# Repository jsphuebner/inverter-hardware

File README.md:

# inverter-hardware
Eagle schematics of inverter main board, sensor boards and gate drivers

# License
Attribution-ShareAlike 4.0 International
https://creativecommons.org/licenses/by-sa/4.0/legalcode

You musn't change the copyright info (J. Huebner and openinverter.org) on the silkscreen in size location or content.

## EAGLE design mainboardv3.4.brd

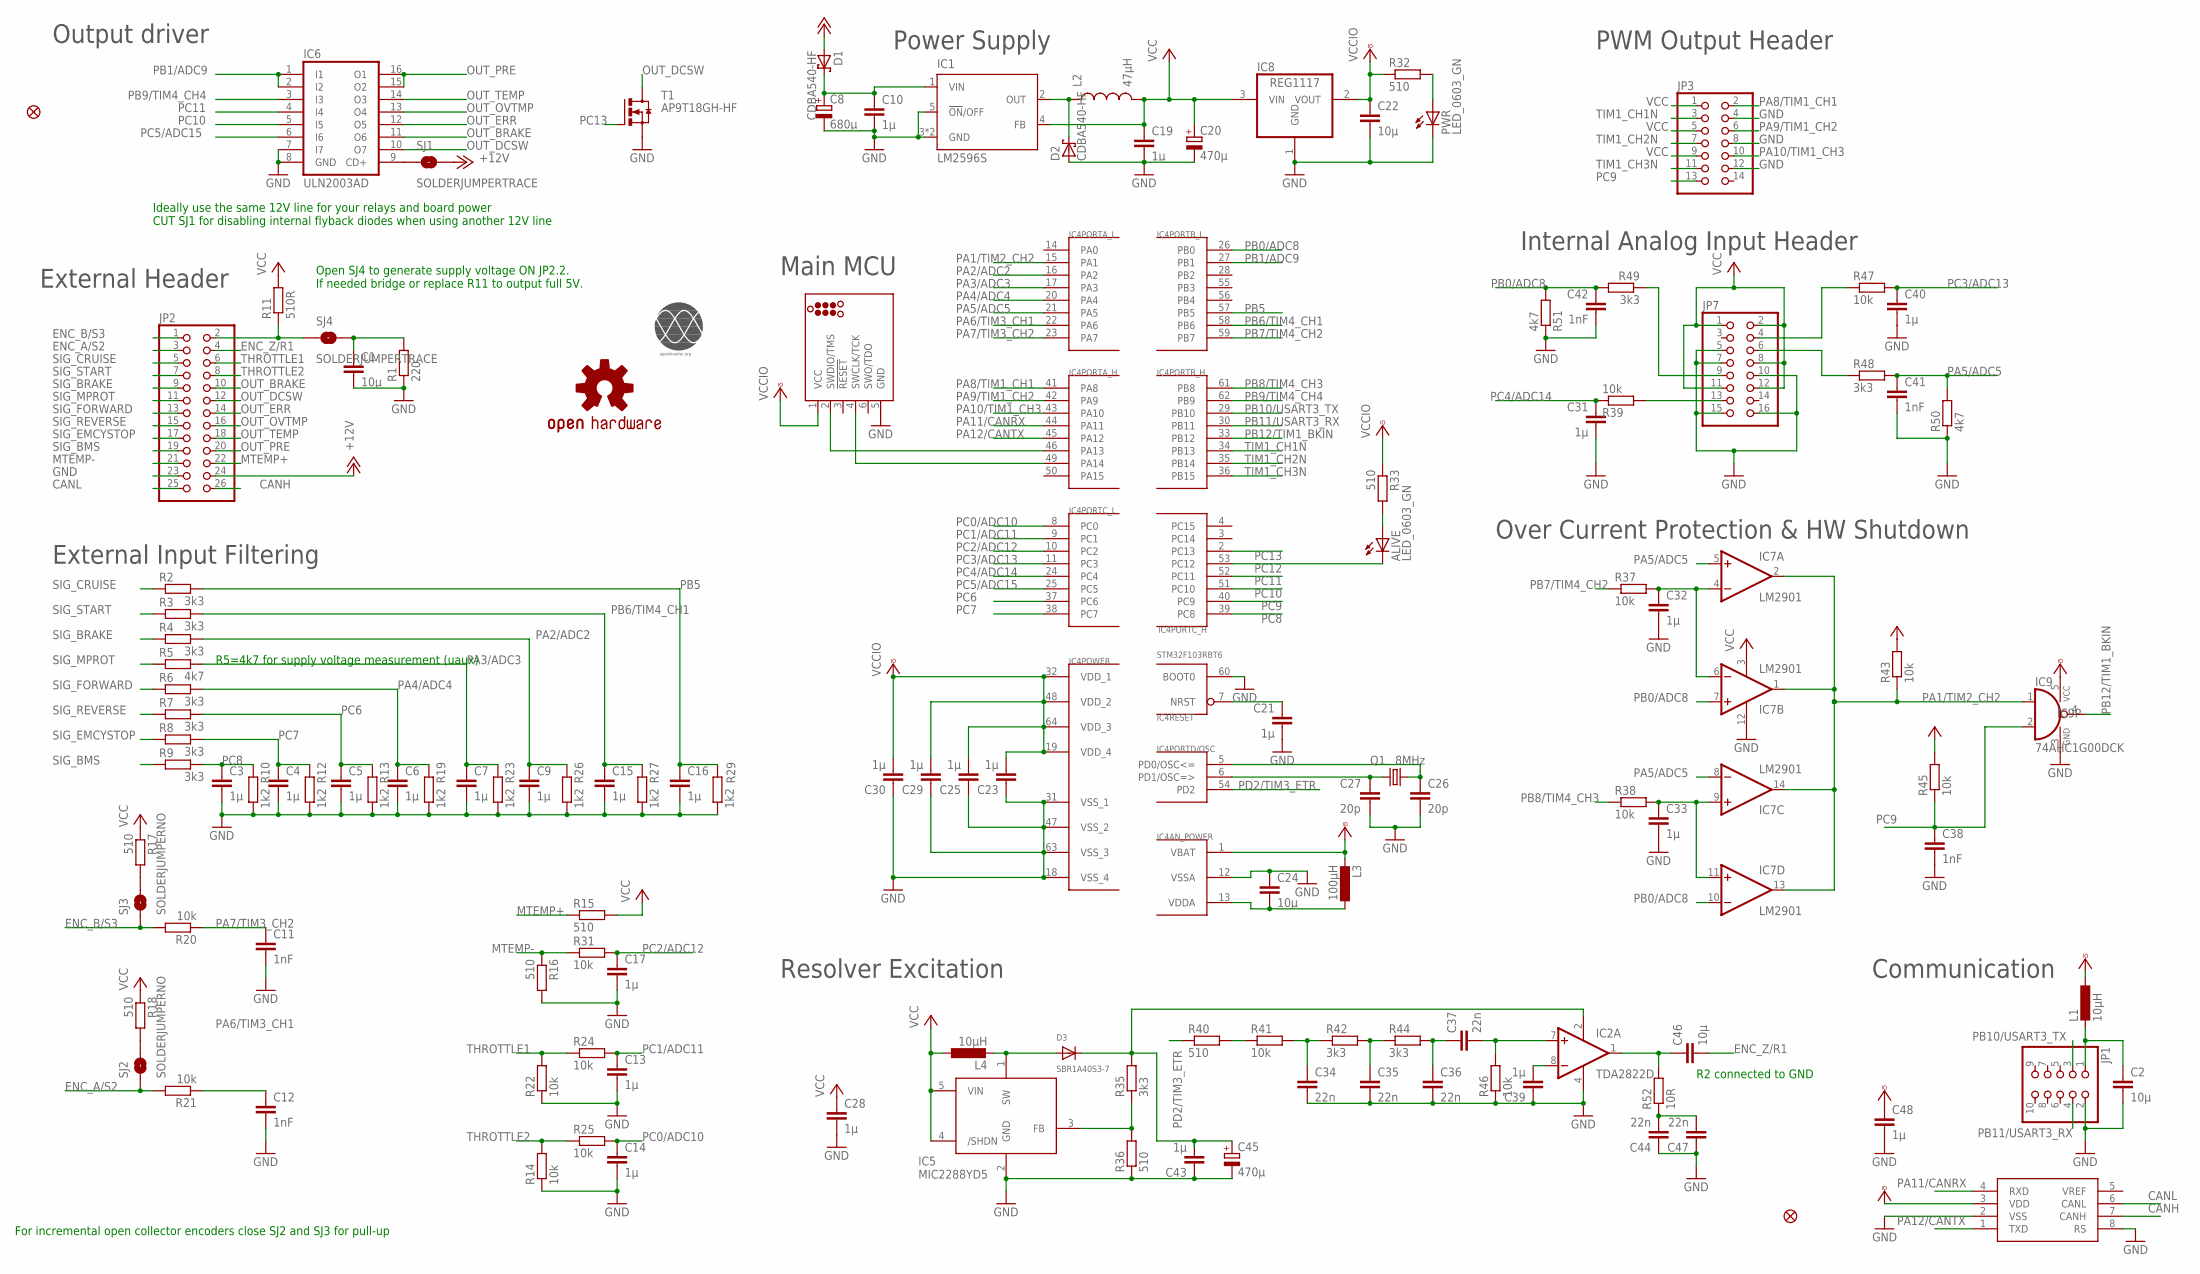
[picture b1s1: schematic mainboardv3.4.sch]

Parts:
ALIVE: LED_0603_GN; SML0805
C1, C2, C22, C46: 10µ; C0805
C3, C4, C5, C6, C7, C9, C10, C13, C14, C15, C16, C17, C19, C21, C23, C25, C28, C29, C30, C31, C32, C33, C39, C40, C43, C48: 1µ; C0603
C8: 680µ; UD-10X10_NICHICON
C11, C12, C38, C41, C42: 1nF; C0603
C20, C45: 470µ; UD-6,3X7,7_NICHICON
C24: 10µ; C0603
C26, C27: 20p; C0603
C34, C35, C36, C37, C44, C47: 22n; C0603
D1, D2: CDBA540-HF; SMB
D3: SBR1A40S3-7; SOD-323F
FID1, FID2: FIDUCIAL1X2.5; FIDUCIAL-1X2.5
IC1: LM2596S; TO263-5
IC2: TDA2822D; SO08
IC3: SN65HVD230DR; SO08
IC4: STM32F103RBT6; TQFP64
IC5: MIC2288YD5; SOT23-5L
IC6: ULN2003AD; SO16
IC7: LM2901; SO14
IC8: REG1117; SOT223
IC9: 74AHC1G00DCK; SC70-5
J1: TC2030_SWD-MCP; TC2030-MCP
JP1: PINHD-2X5/90; 2X05/90
JP2: PINHD-2X13; 2X13
JP3: PINHD-2X7; 2X07
JP7: PINHD-2X8; 2X08
L1: 10µH; L2012C
L2: 47µH; CDRH125
L3: 100µH; L2012C
L4: 10µH; L2825P
LOGO1: OSHW-LOGOM; OSHW-LOGO-M
PWR: LED_0603_GN; SML0805
Q1: 8MHz; CRYSTAL-TXC-7A
R1: 220; R0603
R2, R3, R4, R6, R7, R8, R9, R35, R42, R44, R48, R49: 3k3; R0603
R5, R50, R51: 4k7; R0603
R10, R12, R13, R19, R23, R26, R27, R29: 1k2; R0603
R11: 510R; R0603
R14, R20, R21, R22, R24, R25, R31, R37, R38, R39, R41, R43, R45, R46, R47: 10k; R0603
R15, R16, R17, R18, R32, R33, R36, R40: 510; R0603
R52: 10R; R0603
SJ1, SJ4: SOLDERJUMPERTRACE; SJ_2S-TRACE
SJ2, SJ3: SOLDERJUMPERNO; SJ_2S-NO
T1: AP9T18GH-HF; D-PAK_TO252AA
U$1: OI-LOGO; OI_LOGO

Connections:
+12V: D1.A, JP2.24, SJ1.2
CANH: IC3.7 (CANH), JP2.26
CANL: IC3.6 (CANL), JP2.25
ENC_A/S2: JP2.3, R21.2, SJ2.1
ENC_B/S3: JP2.1, R20.2, SJ3.1
ENC_Z/R1: C46.2, JP2.4
GND: C1.2, C2.2, C3.2, C4.2, C5.2, C6.2, C7.2, C8.-, C9.2, C10.2, C11.2, C12.2, C13.2, C14.2, C15.2, C16.2, C17.2, C19.2, C20.-, C21.2, C22.2, C23.1, C24.1, C25.1, C26.2, C27.2, C28.2, C29.1, C30.1, C31.2, C32.2, C33.2, C34.2, C35.2, C36.2, C38.2, C39.1, C40.2, C41.2, C42.2, C43.1, C44.1, C45.-, C47.1, C48.2, D2.A, IC1.3 (GND), IC1.5 (!ON!/OFF), IC1.6 (GND), IC2.4 (V-), IC3.2 (VSS), IC3.8 (RS), IC4.12 (VSSA), IC4.18 (VSS_4), IC4.31 (VSS_1), IC4.47 (VSS_2), IC4.60 (BOOT0), IC4.63 (VSS_3), IC5.2 (GND), IC6.7 (I7), IC6.8 (GND), IC7.12 (GND), IC8.1 (GND), IC9.3 (GND), J1.5 (GND), JP1.2, JP2.23, JP3.4, JP3.8, JP3.12, JP7.5, JP7.7, JP7.10, JP7.15, JP7.16, PWR.C, R1.1, R10.1, R12.1, R13.1, R14.1, R16.2, R19.1, R22.1, R23.1, R26.1, R27.1, R29.1, R36.1, R46.1, R50.1, R51.1, T1.3 (S)
I_L1: JP7.6, R48.1
I_L2: JP7.9, R49.1
MTEMP+: JP2.22, R15.1
MTEMP-: JP2.21, R16.1, R31.1
unnamed: IC6.9 (CD+), SJ1.1
unnamed: C27.1, IC4.6 (PD1/OSC=>), Q1.P$1 (1)
unnamed: R17.2, SJ3.2
unnamed: C26.1, IC4.5 (PD0/OSC<=), Q1.P$2 (2)
unnamed: IC4.46 (PA13), J1.2 (SWDIO/TMS)
unnamed: IC4.49 (PA14), J1.4 (SWCLK/TCK)
unnamed: C24.2, IC4.13 (VDDA), L3.1
unnamed: R18.2, SJ2.2
unnamed: C1.1, R1.2, SJ4.2
unnamed: C33.1, IC7.9 (+IN), IC7.11 (+IN), R38.2
unnamed: C44.2, C47.2, R52.1
unnamed: R40.2, R41.1
unnamed: D2.C, IC1.2 (OUT), L2.1
unnamed: C32.1, IC7.4 (-IN), IC7.6 (-IN), R37.2
unnamed: C35.1, R42.2, R44.1
unnamed: C36.1, C37.1, R44.2
unnamed: C37.2, IC2.7 (+IN), R46.2
unnamed: C46.1, IC2.1 (OUT), R52.2
unnamed: C43.2, C45.+, D3.C, IC2.2 (V+), R35.2
unnamed: PWR.A, R32.2
unnamed: ALIVE.A, R33.2
unnamed: IC5.3 (FB), R35.1, R36.2
unnamed: C8.+, C10.1, D1.C, IC1.1 (VIN)
unnamed: D3.A, IC5.1 (SW), L4.2
unnamed: C39.2, IC2.8 (-IN)
unnamed: C2.1, JP1.1, L1.2
unnamed: C34.1, R41.2, R42.1
NRST: C21.1, IC4.7 (NRST)
OUT_BRAKE: IC6.11 (O6), JP2.10
OUT_DCSW: IC6.10 (O7), JP2.12, T1.4 (D)
OUT_ERR: IC6.12 (O5), JP2.14
OUT_OVTMP: IC6.13 (O4), JP2.16
OUT_PRE: IC6.15 (O2), IC6.16 (O1), JP2.20
OUT_TEMP: IC6.14 (O3), JP2.18
PA1/TIM2_CH2: IC4.15 (PA1), IC7.1 (OUT), IC7.2 (OUT), IC7.13 (OUT), IC7.14 (OUT), IC9.1 (I0), R43.1
PA2/ADC2: C9.1, IC4.16 (PA2), R4.2, R26.2
PA3/ADC3: C7.1, IC4.17 (PA3), R5.2, R23.2
PA4/ADC4: C6.1, IC4.20 (PA4), R6.2, R19.2
PA5/ADC5: C41.1, IC4.21 (PA5), IC7.5 (+IN), IC7.8 (-IN), R48.2, R50.2
PA6/TIM3_CH1: C12.1, IC4.22 (PA6), R21.1
PA7/TIM3_CH2: C11.1, IC4.23 (PA7), R20.1
PA8/TIM1_CH1: IC4.41 (PA8), JP3.2
PA9/TIM1_CH2: IC4.42 (PA9), JP3.6
PA10/TIM1_CH3: IC4.43 (PA10), JP3.10
PA11/CANRX: IC3.4 (RXD), IC4.44 (PA11)
PA12/CANTX: IC3.1 (TXD), IC4.45 (PA12)
PB0/ADC8: C42.1, IC4.26 (PB0), IC7.7 (+IN), IC7.10 (-IN), R49.2, R51.2
PB1/ADC9: IC4.27 (PB1), IC6.1 (I1), IC6.2 (I2)
PB5: C16.1, IC4.57 (PB5), R2.2, R29.2
PB6/TIM4_CH1: C15.1, IC4.58 (PB6), R3.2, R27.2
PB7/TIM4_CH2: IC4.59 (PB7), R37.1
PB8/TIM4_CH3: IC4.61 (PB8), R38.1
PB9/TIM4_CH4: IC4.62 (PB9), IC6.3 (I3)
PB10/USART3_TX: IC4.29 (PB10), JP1.3
PB11/USART3_RX: IC4.30 (PB11), JP1.4
PB12/TIM1_BKIN: IC4.33 (PB12), IC9.4 (O)
PC0/ADC10: C14.1, IC4.8 (PC0), R25.2
PC1/ADC11: C13.1, IC4.9 (PC1), R24.2
PC2/ADC12: C17.1, IC4.10 (PC2), R31.2
PC3/ADC13: C40.1, IC4.11 (PC3), R47.2
PC4/ADC14: C31.1, IC4.24 (PC4), R39.1
PC5/ADC15: IC4.25 (PC5), IC6.6 (I6)
PC6: C5.1, IC4.37 (PC6), R7.2, R13.2
PC7: C4.1, IC4.38 (PC7), R8.2, R12.2
PC8: C3.1, IC4.39 (PC8), R9.2, R10.2
PC9: C38.1, IC4.40 (PC9), IC9.2 (I1), JP3.13, R45.1
PC10: IC4.51 (PC10), IC6.5 (I5)
PC11: IC4.52 (PC11), IC6.4 (I4)
PC12: ALIVE.C, IC4.53 (PC12)
PC13: IC4.2 (PC13), T1.1 (G)
PD2/TIM3_ETR: IC4.54 (PD2), R40.1
S4/S1: JP2.2, R11.1, SJ4.1
SIG_BMS: JP2.19, R9.1
SIG_BRAKE: JP2.9, R4.1
SIG_CRUISE: JP2.5, R2.1
SIG_EMCYSTOP: JP2.17, R8.1
SIG_FORWARD: JP2.13, R6.1
SIG_MPROT: JP2.11, R5.1
SIG_REVERSE: JP2.15, R7.1
SIG_START: JP2.7, R3.1
THROTTLE1: JP2.6, R22.2, R24.1
THROTTLE2: JP2.8, R14.2, R25.1
TIM1_CH1N: IC4.34 (PB13), JP3.3
TIM1_CH2N: IC4.35 (PB14), JP3.7
TIM1_CH3N: IC4.36 (PB15), JP3.11
TMPHS: JP7.13, R39.2
UDC: JP7.4, R47.1
VCC: C19.1, C20.+, C28.1, IC1.4 (FB), IC5.4 (/SHDN), IC5.5 (VIN), IC7.3 (V+), IC8.3 (VIN), JP3.1, JP3.5, JP3.9, JP7.1, JP7.2, JP7.8, JP7.11, JP7.12, L2.2, L4.1, R11.2, R15.2, R17.1, R18.1, R43.2, R45.2
VCCIO: C22.1, C23.2, C25.2, C29.2, C30.2, C48.1, IC3.3 (VDD), IC4.1 (VBAT), IC4.19 (VDD_4), IC4.32 (VDD_1), IC4.48 (VDD_2), IC4.64 (VDD_3), IC8.2 (VOUT), IC9.5 (VCC), J1.1 (VCC), L1.1, L3.2, R32.1, R33.1

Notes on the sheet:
Output driver
Resolver Excitation
Over Current Protection & HW Shutdown
For incremental open collector encoders close SJ2 and SJ3 for pull-up
R2 connected to GND
Open SJ4 to generate supply voltage ON JP2.2. If needed bridge or replace R11 to output full 5V.
External Input Filtering
Ideally use the same 12V line for your relays and board power CUT SJ1 for disabling internal flyback diodes when using another 12V line
External Header
Communication
Power Supply
PWM Output Header
Internal Analog Input Header
Main MCU
R5=4k7 for supply voltage measurement (uaux)
IC5 MIC2288YD5

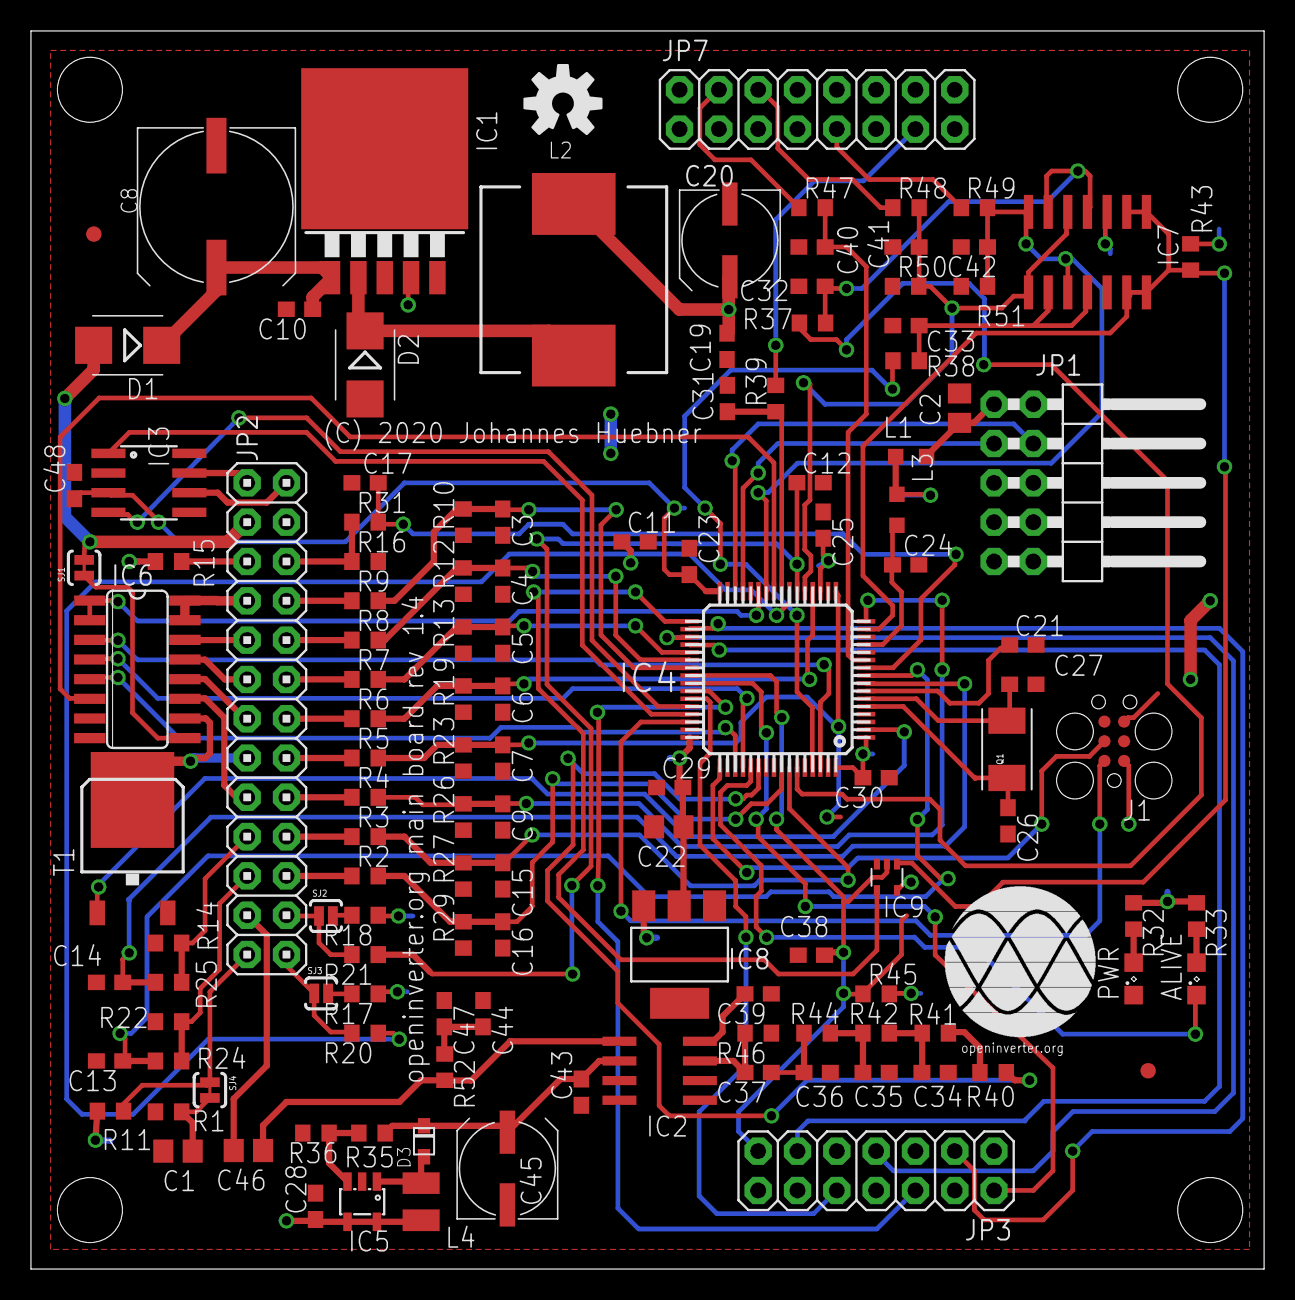
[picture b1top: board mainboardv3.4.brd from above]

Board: 2 copper layers, 79.7 x 80.0 mm, 129 parts (0 on the bottom side), 100 nets.

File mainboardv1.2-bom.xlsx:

Designator | Comment | Package | LCSC Part #
ALIVE, PWR | LED_0603_GN | CHIPLED-0805 | C84256
C1, C2, C22, C46 | 10uF | C0805 | C15850
C11, C12, C12, C38, C41, C42 | 1nF | C0603 | C46653
C8 | 470uF | SMD-ECAP-10x10 | C249931 | e
C20 | 470uF | SMD-ECAP-6.3X7.7 | C134738 | e
C45 | 330uF | SMD-ECAP-6.3X7.7 | C134823 | e
C26, C27 | 22p | C0603 | C1804
C3, C4, C5, C6, C7, C9, C10, C13, C14, C15, C16, C17, C19, C21, C23, C24, C25, 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 | 1uF | C0603 | C28323
C34, C35, C36, C37, C44, C47 | 22n | C0603 | C21122
D1, D2 | CDBA540-HF | SMB | C22452
D3 | SBR1A40S3-7 | SOD-323F | C2128
IC1 | LM2596S | TO263-5 | C10002
IC2 | TDA2822D | SO08 | C73296 | e
IC3 | MCP2562P | SO08 | C53609 | e
IC4 | STM32F103RBT6 | LQFP-64_10.0x10.0x0.5P | C8735
IC5 | MIC2288YD5 | SOT23-5L | C7722
IC6 | ULN2003AD | SO16 | C7512
IC7 | LM2901 | SO14 | C142961 | e
IC8 | REG1117 | SOT-223 | C347229
IC9 | SN74LVC1G10 | SOT-23-6 | C258149 | e
JP6 | 1365-10 | con-leotronics
L1, L3 | 10uH | L0805 | C1046
L4 | 10uH | L1210 | C86069 | e
L2 | 47uH | SMD-PIND-12.5x12.5x8_2.9x5.4 | C169376 | e
Q1 | 8MHz | SMD-5032_2P | C115962
R1 | 220Ω | R0603 | C22962
R10, R12, R13, R19, R23, R26, R27, R29 | 1.2KΩ | R0603 | C22765
R11, R15, R16, R32, R33, R36, R40 | 510Ω | R0603 | C23193
R14,R20, R21, R22, R24, R25, R31, R34, R37, R38, R39, R41, R43, R45, R46, R47 | 10KΩ | R0603 | C17414
R2, R3, R3, R4, R6, R7, R8, R9, R35, R42, R44, R48, R49 | 3.3KΩ | R0603 | C26010
R5, R50, R51 | 4.7KΩ | R0603 | C17673
R52 | 10Ω | R0603 | C22859

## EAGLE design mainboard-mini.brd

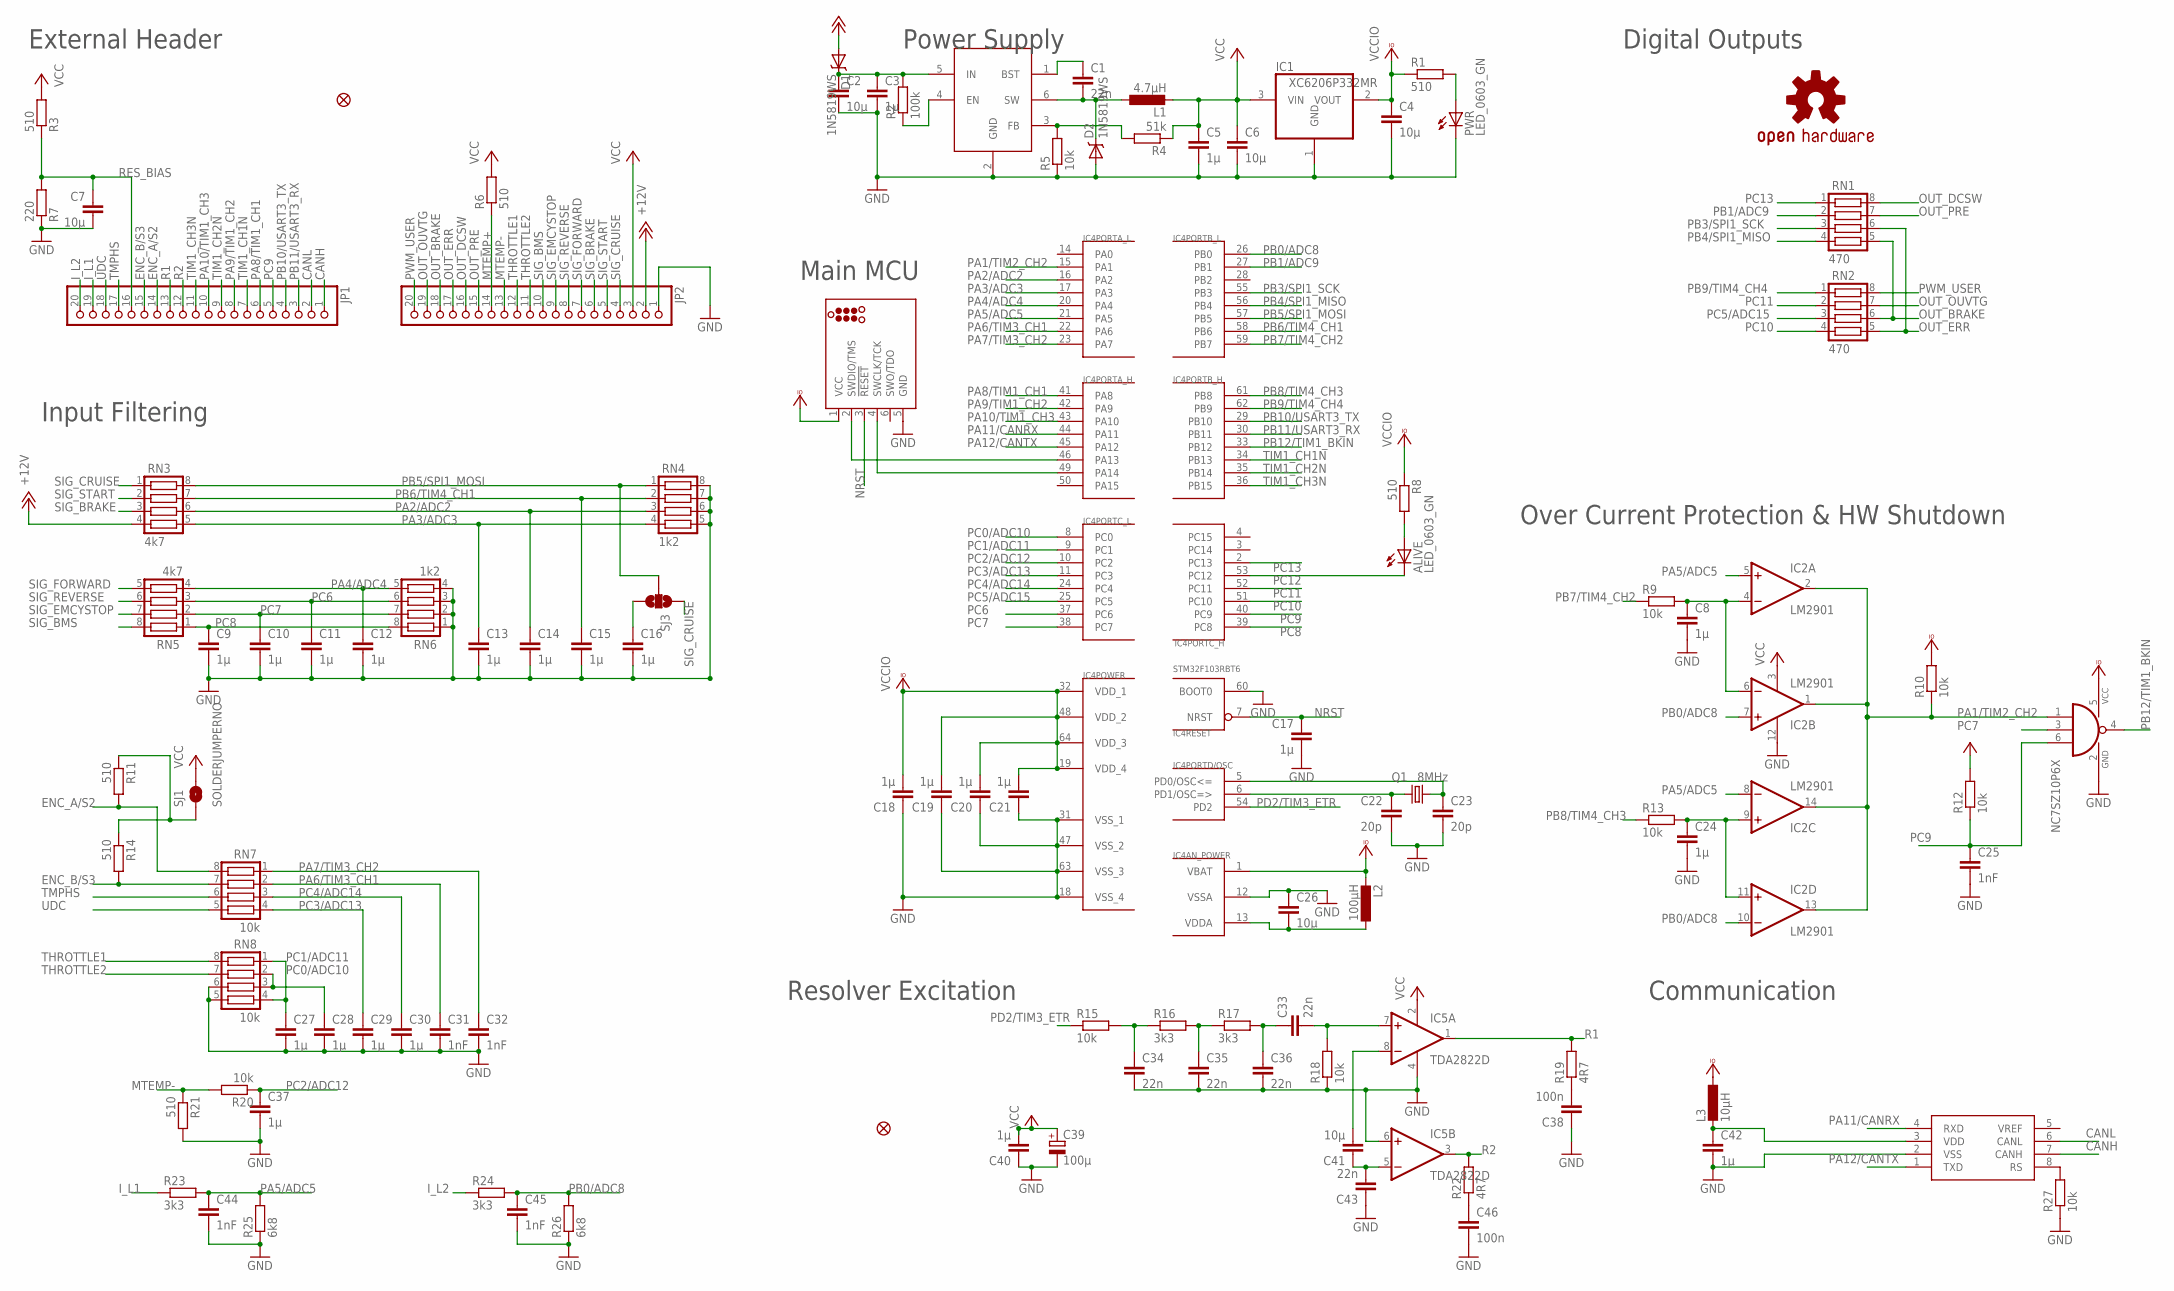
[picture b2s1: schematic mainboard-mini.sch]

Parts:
ALIVE: LED_0603_GN; SML0805
C1, C33, C34, C35, C36, C43: 22n; C0603
C2, C4, C6, C7, C26, C41: 10µ; C0603
C3, C5, C8, C9, C10, C11, C12, C13, C14, C15, C16, C17, C18, C19, C20, C21, C24, C27, C28, C29, C30, C37, C40, C42: 1µ; C0603
C22, C23: 20p; C0603
C25, C31, C32, C44, C45: 1nF; C0603
C38, C46: 100n; C0603
C39: 100µ; B/3528-21R
D1, D2: 1N5819WS; SOD-323
FID1, FID2: FIDUCIAL1X2.5; FIDUCIAL-1X2.5
IC1: XC6206P332MR; SOT223
IC2: LM2901; SO14
IC3: NC7SZ10P6X; SC70-6
IC4: STM32F103RBT6; TQFP64
IC5: TDA2822D; SO08
IC6: SN65HVD230; SO08
IC7: RT8259GE; SOT23-6
J1: TC2030_SWD-MCP; TC2030-MCP
JP1, JP2: PINHD-1X20; 1X20
L1: 4.7µH; L2825P
L2: 100µH; L2012C
L3: 10µH; L2012C
LOGO1: OSHW-LOGOM; OSHW-LOGO-M
PWR: LED_0603_GN; SML0805
Q1: 8MHz; CRYSTAL-TXC-7A
R1, R3, R6, R8, R11, R14, R21: 510; R0603
R2: 100k; R0603
R4: 51k; R0603
R5, R9, R10, R12, R13, R15, R18, R20, R27: 10k; R0603
R7: 220; R0603
R16, R17, R23, R24: 3k3; R0603
R19, R22: 4R7; R0603
R25, R26: 6k8; R0603
RN1, RN2: 470; CTS742C083
RN3, RN5: 4k7; CTS742C083
RN4, RN6: 1k2; CTS742C083
RN7, RN8: 10k; CTS742C083
SJ1: SOLDERJUMPERNO; SJ_2S-NO
SJ3: SOLDERJUMPER_2WAYPASTE2&3; SJ_3_PASTE2&3

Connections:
+12V: D1.2 (A), JP2.2, RN3.4
CANH: IC6.7 (CANH), JP1.1
CANL: IC6.6 (CANL), JP1.2
ENC_A/S2: JP1.14, R11.2, RN7.8
ENC_B/S3: JP1.15, R14.2, RN7.7
GND: C2.2, C3.2, C4.2, C5.2, C6.2, C7.2, C8.2, C9.2, C10.2, C11.2, C12.2, C13.2, C14.2, C15.2, C16.2, C17.2, C18.1, C19.1, C20.1, C21.1, C22.2, C23.2, C24.2, C25.2, C26.1, C27.2, C28.2, C29.2, C30.2, C31.2, C32.2, C34.2, C35.2, C36.2, C37.2, C38.1, C39.-, C40.1, C42.2, C43.1, C44.2, C45.2, C46.2, D2.2 (A), IC1.1 (GND), IC2.12 (GND), IC3.2 (GND), IC4.12 (VSSA), IC4.18 (VSS_4), IC4.31 (VSS_1), IC4.47 (VSS_2), IC4.60 (BOOT0), IC4.63 (VSS_3), IC5.4 (V-), IC5.6 (+IN), IC6.2 (VSS), IC7.2 (GND), J1.5 (GND), JP2.1, PWR.C, R5.1, R7.1, R18.1, R21.2, R25.1, R26.1, R27.1, RN4.5, RN4.6, RN4.7, RN4.8, RN6.1, RN6.2, RN6.3, RN6.4, RN8.5, RN8.6
I_L1: JP1.19, R23.1
I_L2: JP1.20, R24.1
MTEMP+: JP2.14, R6.1
MTEMP-: JP2.13, R20.2, R21.1
unnamed: C41.1, C43.2, IC5.5 (-IN)
unnamed: C22.1, IC4.6 (PD1/OSC=>), Q1.P$1 (1)
unnamed: C2.1, C3.1, D1.1 (C), IC7.5 (IN), R2.2
unnamed: C23.1, IC4.5 (PD0/OSC<=), Q1.P$2 (2)
unnamed: C1.1, IC7.1 (BST)
unnamed: IC4.46 (PA13), J1.2 (SWDIO/TMS)
unnamed: C26.2, IC4.13 (VDDA), L2.1
unnamed: IC7.4 (EN), R2.1
unnamed: IC4.49 (PA14), J1.4 (SWCLK/TCK)
unnamed: C24.1, IC2.9 (+IN), IC2.11 (+IN), R13.2
unnamed: C38.2, R19.1
unnamed: C41.2, IC5.8 (-IN)
unnamed: IC7.3 (FB), R4.2, R5.2
unnamed: C1.2, D2.1 (C), IC7.6 (SW), L1.1
unnamed: C8.1, IC2.4 (-IN), IC2.6 (-IN), R9.2
unnamed: C42.1, IC6.3 (VDD), L3.2
unnamed: C35.1, R16.2, R17.1
unnamed: C33.1, C36.1, R17.2
unnamed: C33.2, IC5.7 (+IN), R18.2
unnamed: R11.1, R14.1, SJ1.1
unnamed: C16.1, SJ3.3
unnamed: PWR.A, R1.2
unnamed: ALIVE.A, R8.2
unnamed: IC6.8 (RS), R27.2
unnamed: C46.1, R22.1
unnamed: C34.1, R15.2, R16.1
NRST: C17.1, IC4.7 (NRST), J1.3 (!RESET)
OUT_BRAKE: JP2.18, RN1.5, RN2.6
OUT_DCSW: JP2.16, RN1.8
OUT_ERR: JP2.17, RN1.6, RN2.5
OUT_OUVTG: JP2.19, RN2.7
OUT_PRE: JP2.15, RN1.7
PA1/TIM2_CH2: IC2.1 (OUT), IC2.2 (OUT), IC2.13 (OUT), IC2.14 (OUT), IC3.1 (I0), IC4.15 (PA1), R10.1
PA2/ADC2: C14.1, IC4.16 (PA2), RN3.6, RN4.3
PA3/ADC3: C13.1, IC4.17 (PA3), RN3.5, RN4.4
PA4/ADC4: C12.1, IC4.20 (PA4), RN5.4, RN6.5
PA5/ADC5: C44.1, IC2.5 (+IN), IC2.8 (-IN), IC4.21 (PA5), R23.2, R25.2
PA6/TIM3_CH1: C31.1, IC4.22 (PA6), RN7.2
PA7/TIM3_CH2: C32.1, IC4.23 (PA7), RN7.1
PA8/TIM1_CH1: IC4.41 (PA8), JP1.6
PA9/TIM1_CH2: IC4.42 (PA9), JP1.8
PA10/TIM1_CH3: IC4.43 (PA10), JP1.10
PA11/CANRX: IC4.44 (PA11), IC6.4 (RXD)
PA12/CANTX: IC4.45 (PA12), IC6.1 (TXD)
PB0/ADC8: C45.1, IC2.7 (+IN), IC2.10 (-IN), IC4.26 (PB0), R24.2, R26.2
PB1/ADC9: IC4.27 (PB1), RN1.2
PB3/SPI1_SCK: IC4.55 (PB3), RN1.3
PB4/SPI1_MISO: IC4.56 (PB4), RN1.4
PB5/SPI1_MOSI: IC4.57 (PB5), RN3.8, RN4.1, SJ3.2
PB6/TIM4_CH1: C15.1, IC4.58 (PB6), RN3.7, RN4.2
PB7/TIM4_CH2: IC4.59 (PB7), R9.1
PB8/TIM4_CH3: IC4.61 (PB8), R13.1
PB9/TIM4_CH4: IC4.62 (PB9), RN2.1
PB10/USART3_TX: IC4.29 (PB10), JP1.4
PB11/USART3_RX: IC4.30 (PB11), JP1.3
PB12/TIM1_BKIN: IC3.4 (O), IC4.33 (PB12)
PC0/ADC10: C28.1, IC4.8 (PC0), RN8.2, RN8.3
PC1/ADC11: C27.1, IC4.9 (PC1), RN8.1, RN8.4
PC2/ADC12: C37.1, IC4.10 (PC2), R20.1
PC3/ADC13: C29.1, IC4.11 (PC3), RN7.4
PC4/ADC14: C30.1, IC4.24 (PC4), RN7.3
PC5/ADC15: IC4.25 (PC5), RN2.3
PC6: C11.1, IC4.37 (PC6), RN5.3, RN6.6
PC7: C10.1, IC3.3 (I1), IC4.38 (PC7), RN5.2, RN6.7
PC8: C9.1, IC4.39 (PC8), RN5.1, RN6.8
PC9: C25.1, IC3.6 (I2), IC4.40 (PC9), JP1.5, R12.1
PC10: IC4.51 (PC10), RN2.4
PC11: IC4.52 (PC11), RN2.2
PC12: ALIVE.C, IC4.53 (PC12)
PC13: IC4.2 (PC13), RN1.1
PD2/TIM3_ETR: IC4.54 (PD2), R15.1
PWM_USER: JP2.20, RN2.8
R1: IC5.1 (OUT), JP1.13, R19.2
R2: IC5.3 (OUT), JP1.12, R22.2
RES_BIAS: C7.1, JP1.16, R3.1, R7.2
SIG_BMS: JP2.10, RN5.8
SIG_BRAKE: JP2.6, RN3.3
SIG_CRUISE: JP2.4, RN3.1, SJ3.1
SIG_EMCYSTOP: JP2.9, RN5.7
SIG_FORWARD: JP2.7, RN5.5
SIG_REVERSE: JP2.8, RN5.6
SIG_START: JP2.5, RN3.2
THROTTLE1: JP2.12, RN8.8
THROTTLE2: JP2.11, RN8.7
TIM1_CH1N: IC4.34 (PB13), JP1.7
TIM1_CH2N: IC4.35 (PB14), JP1.9
TIM1_CH3N: IC4.36 (PB15), JP1.11
TMPHS: JP1.17, RN7.6
UDC: JP1.18, RN7.5
VCC: C5.1, C6.1, C39.+, C40.2, IC1.3 (VIN), IC2.3 (V+), IC5.2 (V+), JP2.3, L1.2, R3.2, R4.1, R6.2, R12.2, SJ1.2
VCCIO: C4.1, C18.2, C19.2, C20.2, C21.2, IC1.2 (VOUT), IC3.5 (VCC), IC4.1 (VBAT), IC4.19 (VDD_4), IC4.32 (VDD_1), IC4.48 (VDD_2), IC4.64 (VDD_3), J1.1 (VCC), L2.2, L3.1, R1.1, R8.1, R10.2

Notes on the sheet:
Over Current Protection & HW Shutdown
Input Filtering
External Header
Communication
Power Supply
Digital Outputs
Main MCU
Resolver Excitation

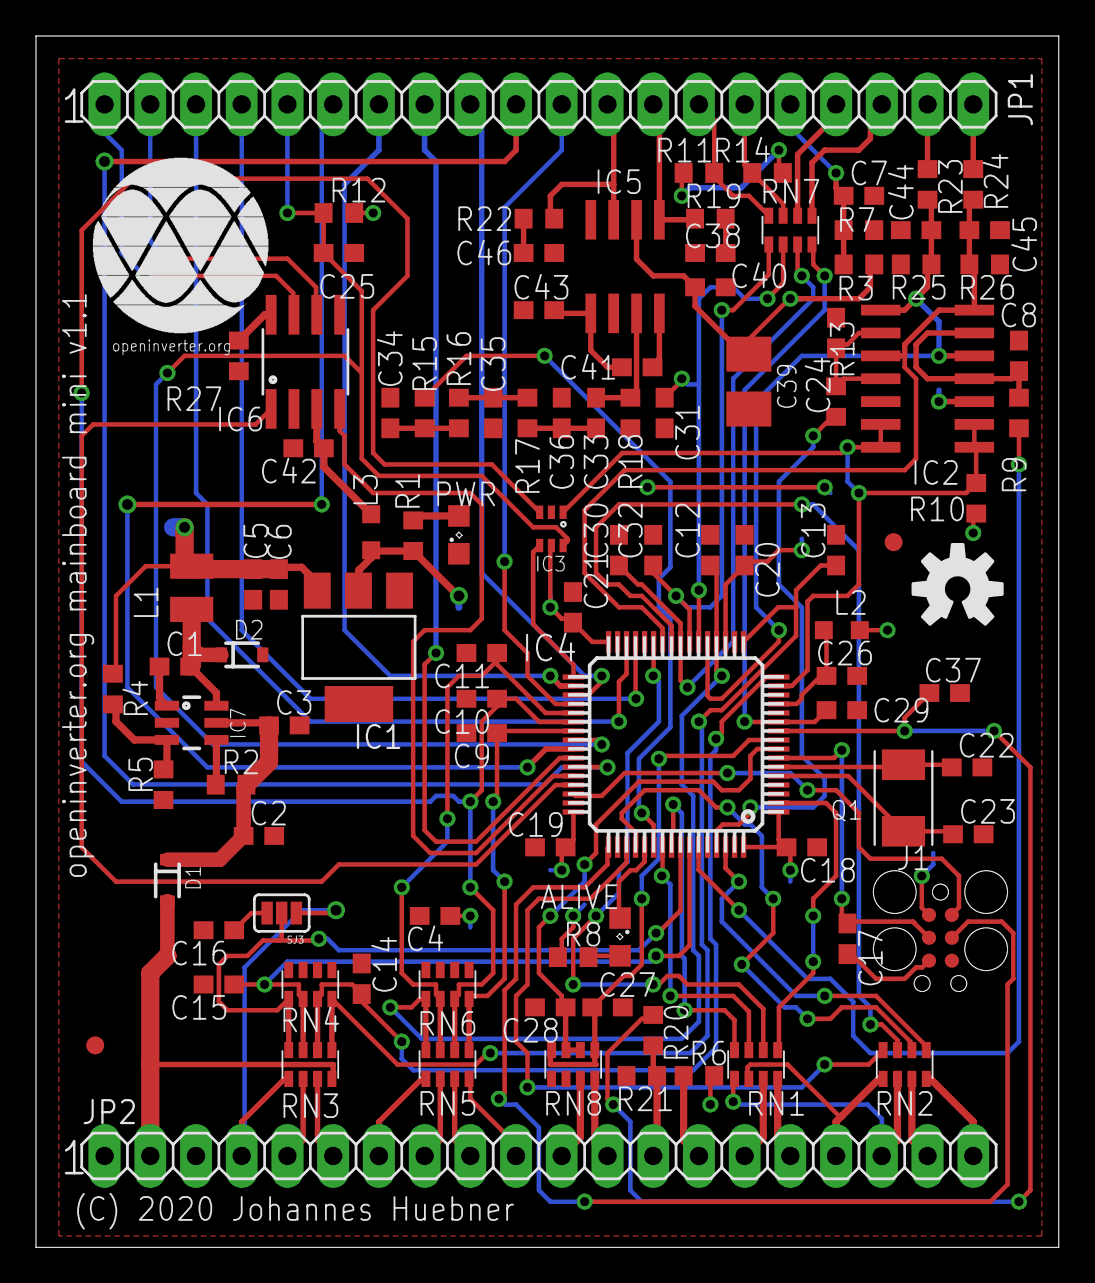
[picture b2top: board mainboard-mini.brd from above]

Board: 2 copper layers, 56.8 x 67.3 mm, 105 parts (1 on the bottom side), 101 nets.

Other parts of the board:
U$2: OI_LOGO

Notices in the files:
base_board6.brd:
(c) 2017
gate_driver2.brd:
(c) 2018 Johannes Huebner
mainboard-mini.brd:
(C) 2020 Johannes Huebner
prius-gen2-v1.0.brd:
(C) 2026 Johannes Huebner
sensor_board2.brd:
(c) 2013 Johannes Huebner
sensor_board3.brd:
(c) 2016 Johannes Huebner
voltage_meas.brd:
(c) 2018 J. Huebner
parts and their libraries:
SparkFun-DigitalIC: Licensing: CC v3.0 Share-Alike You are welcome to use this library for commercial purposes.
tag-connect: ©2009 ROFA.cz - modified and updated by Robert Darlington ‹rdarlington@gmail.com›
